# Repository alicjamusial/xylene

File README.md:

# Xylene - DIP-8/16 flash adapter

### ◾ About the project

Xylene is a SPI NOR flash DIP-8/16 adapter with all needed resistors and capacitors. Using it as the wrapper for flash prevents random errors connected to the power supply and ensures proper behavior of the component.

Board was designed using [KiCad 5.1.6](https://kicad.org/).

### ◾ License
Xylene is available on Creative Commons Attribution Share Alike 4.0 International license (more in [license file](LICENSE.txt)). You are free to use it, modify it and produce as many of your own boards as you need :)

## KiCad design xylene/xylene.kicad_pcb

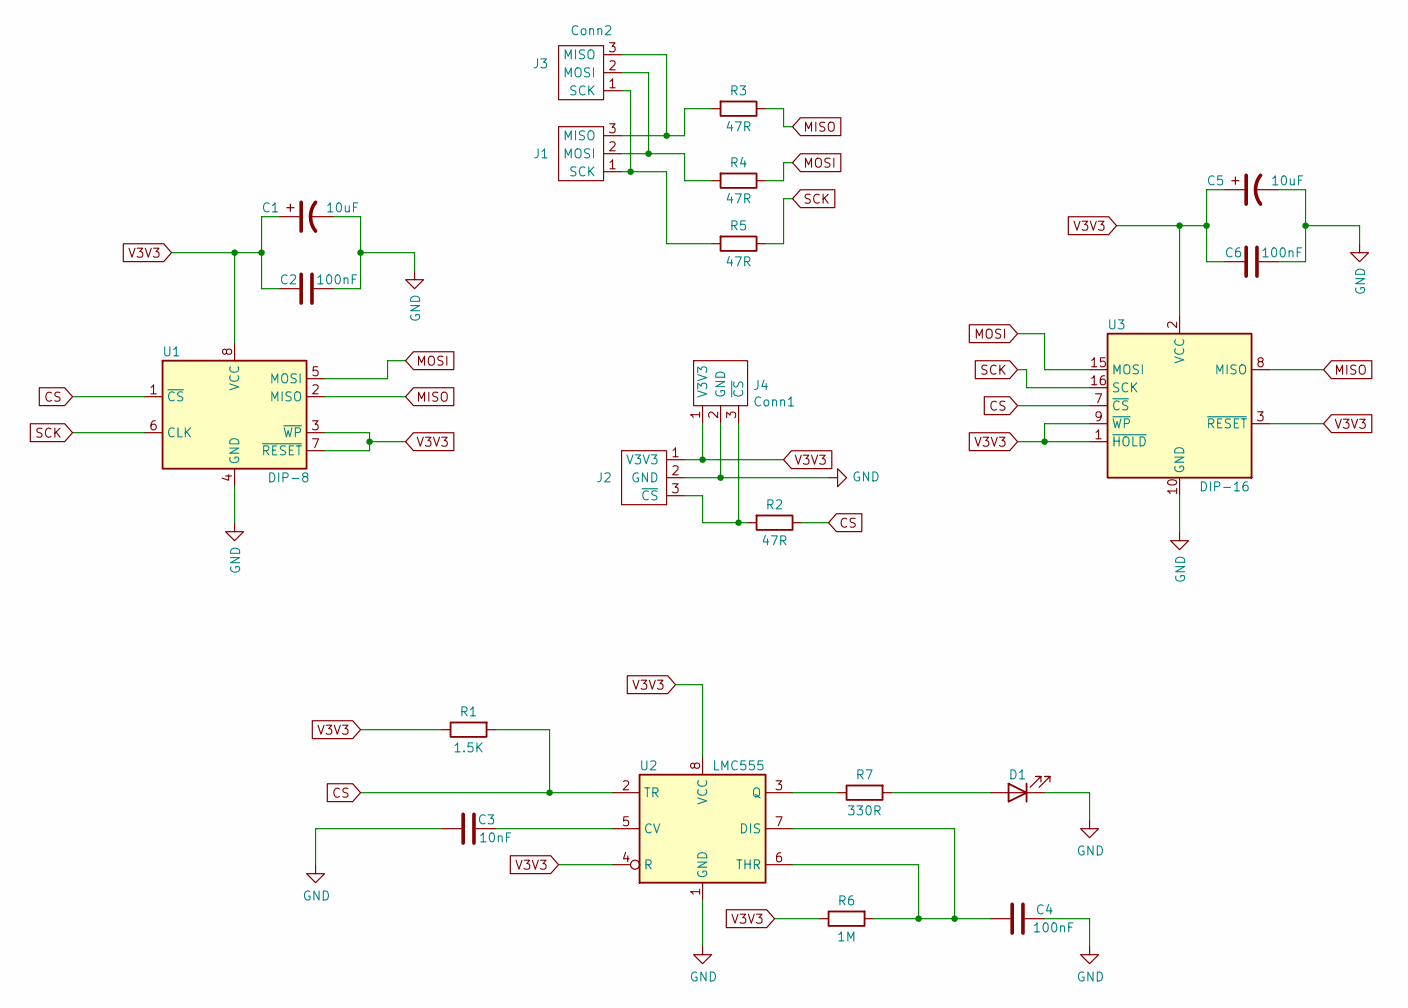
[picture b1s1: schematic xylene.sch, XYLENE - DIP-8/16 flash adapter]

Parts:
C1, C5: 10uF; CP_EIA-3216-18_Kemet-A
C2, C4, C6: 100nF; C_0603_1608Metric
C3: 10nF; C_0603_1608Metric
D1: LED; LED_0805_2012Metric
J1, J3: Conn2; PinHeader_1x03_P2.54mm_Vertical
J2, J4: Conn1; PinHeader_1x03_P2.54mm_Vertical
R1: 1.5K; R_0603_1608Metric
R2, R3, R4, R5: 47R; R_0603_1608Metric
R6: 1M; R_0603_1608Metric
R7: 330R; R_0603_1608Metric
U1: DIP-8; DIP-8_W7.62mm_Socket_wihtout_lines
U2: LMC555; SO-8_3.9x4.9mm_P1.27mm
U3: DIP-16; DIP-16_W15.24mm_without_lines

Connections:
CS: R1.2, R2.1, U1.1 (~CS), U2.2 (TR), U3.7 (~CS)
GND: C1.2, C2.1, C3.1, C4.2, C5.2, C6.1, D1.1 (K), J2.2 (GND), J4.2 (GND), U1.4 (GND), U2.1 (GND), U3.10 (GND)
MISO: R3.1, U1.2 (MISO), U3.8 (MISO)
MOSI: R4.1, U1.5 (MOSI), U3.15 (MOSI)
unnamed: C3.2, U2.5 (CV)
unnamed: C4.1, R6.2, U2.6 (THR), U2.7 (DIS)
unnamed: D1.2 (A), R7.2
unnamed: J1.1 (SCK), J3.1 (SCK), R5.2
unnamed: J1.2 (MOSI), J3.2 (MOSI), R4.2
unnamed: J1.3 (MISO), J3.3 (MISO), R3.2
unnamed: J2.3 (~CS), J4.3 (~CS), R2.2
unnamed: R7.1, U2.3 (Q)
SCK: R5.1, U1.6 (CLK), U3.16 (SCK)
V3V3: C1.1, C2.2, C5.1, C6.2, J2.1 (V3V3), J4.1 (V3V3), R1.1, R6.1, U1.3 (~WP), U1.7 (~RESET), U1.8 (VCC), U2.4 (R), U2.8 (VCC), U3.1 (~HOLD), U3.2 (VCC), U3.3 (~RESET), U3.9 (~WP)

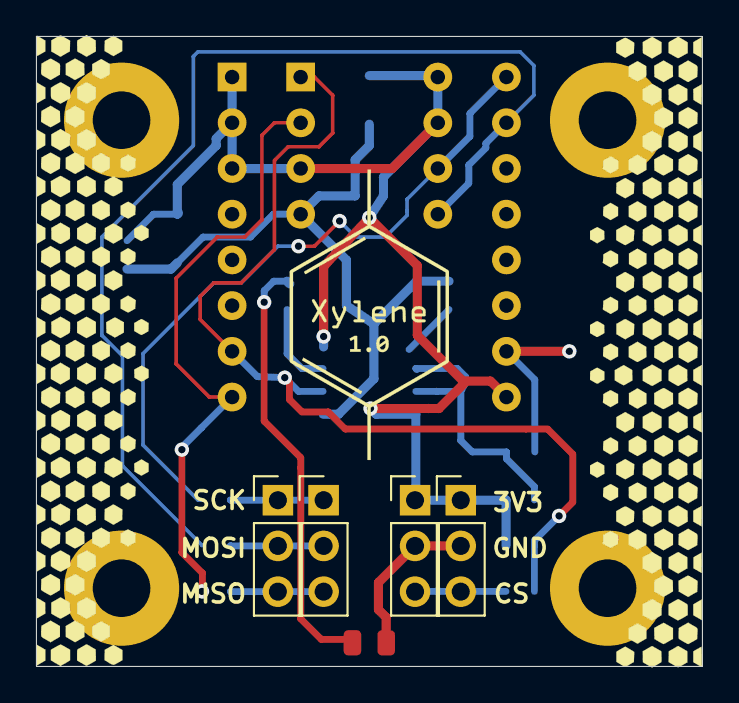
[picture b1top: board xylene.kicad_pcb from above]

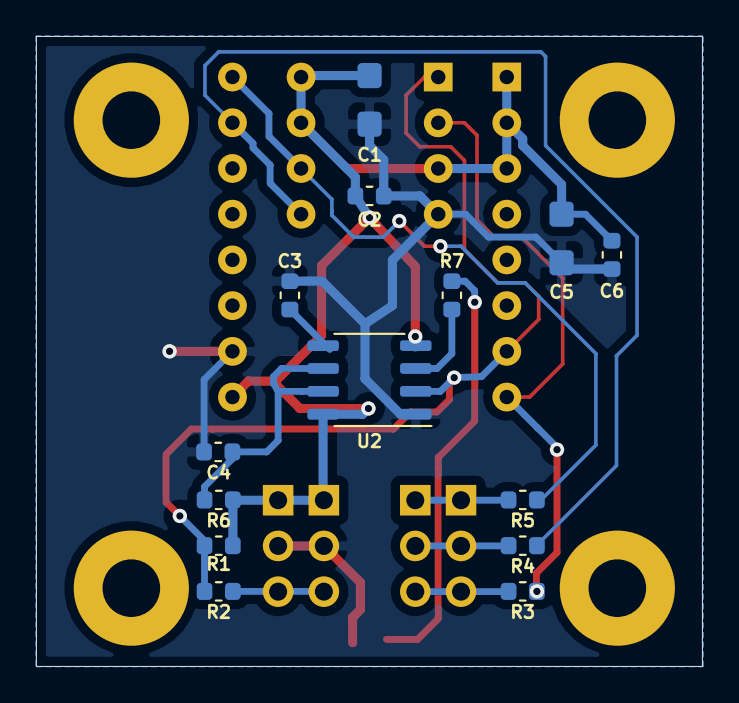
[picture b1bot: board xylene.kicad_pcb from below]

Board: 2 copper layers, 37.0 x 35.0 mm, 21 parts (14 on the bottom side), 14 nets.

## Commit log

2021-04-26 Xylene - repo init
2021-04-26 Add holes
2021-04-26 All components
2021-04-26 Xylene
2021-04-26 Rename project & add readme
2021-04-26 Change 555 to SO-8
2021-04-26 Add renders
2021-04-26 Add second pins for logic analyzer
2021-04-26 Clean images
2021-04-26 Clean
2021-11-08 Update README.md
    https://forum.kicad.info/t/warning-avoid-all-links-to-kicad-pcb-org-use-kicad-org/31521
